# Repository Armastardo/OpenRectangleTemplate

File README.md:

# Open Rectangle Template
**RP2040 template for use with box style controllers for the GC**

## Table of contents
* [About](#about)
* [Usage](#usage)
* [Featured projects](#projects)
* [To-do](#to-do)
* [Acknowledgements](#acknowledgements)

## About
This template was created for the purpose of easing development of box-styled controllers (rectangles) that work with a GameCube console and Nintendo 64 via a USB C to console cable. It uses a RP2040 as its main controller so compatibility to other devices will be limited to the firmware you are using. (Such as [HayBox](https://github.com/JonnyHaystack/HayBox), [Pico-Rectangle](https://github.com/JulienBernard3383279/pico-rectangle), etc). There's already a footprint added for a compatible USB-C port that will allow you to used said cables, as well as a USB C to C cable, or C to A cable for PC or Switch.

Labels are already assigned to the default pinout of the most popular firmware available as well as in stock parts for every component from LCSC. I recommend using the Fabrication Toolkit plugin that can be installed through KiCad's PCM.

## Usage
This templates requires for you to have a minium experience with Kicad and some EE basics. You can just download it as .zip and start creating your own. Make sure you are using **Kicad 7**.
- Download as a zip or clone the repository.
- Open KiCad (7 or newer!) and go to File -> New Project from Template
- Select the tab "User Templates" and click on the Folder icon top right.
- Look for the directory where the kicad project is and open it.
- Template should load. Just click OK and everything will be imported into your project.

## To-do:
- Write a more extensive guide.
- Feature more projects.

## Projects
Small section to highlight proyects that were devveloped using this template.
- [Open Rectangle Breakout](https://github.com/Armastardo/OpenRectangleBreakout) - Breakout board designed to make handwired builds easier.

## Acknowledgements:
- [@Sleepdealr](https://github.com/Sleepdealr/) - For creating the [RP2040 design guide](https://github.com/Sleepdealr/RP2040-designguide) which this template is mostly based from
- Crane's Lab - For having such an amazing community and inspiring creativity in everyone who steps there.
- [@rana-sylvatica](https://github.com/rana-sylvatica/) - For making the OFOF1/Rana Digital and inspiring me to design my rectangles.
- [@Ryanemzed](https://github.com/Ryanemzed/) - For posting a cool clear acrylic build and taking me into a new rabbit hole (and being an amazing community member!).
- The Phob project - For being an amazing standard for the open source-community.

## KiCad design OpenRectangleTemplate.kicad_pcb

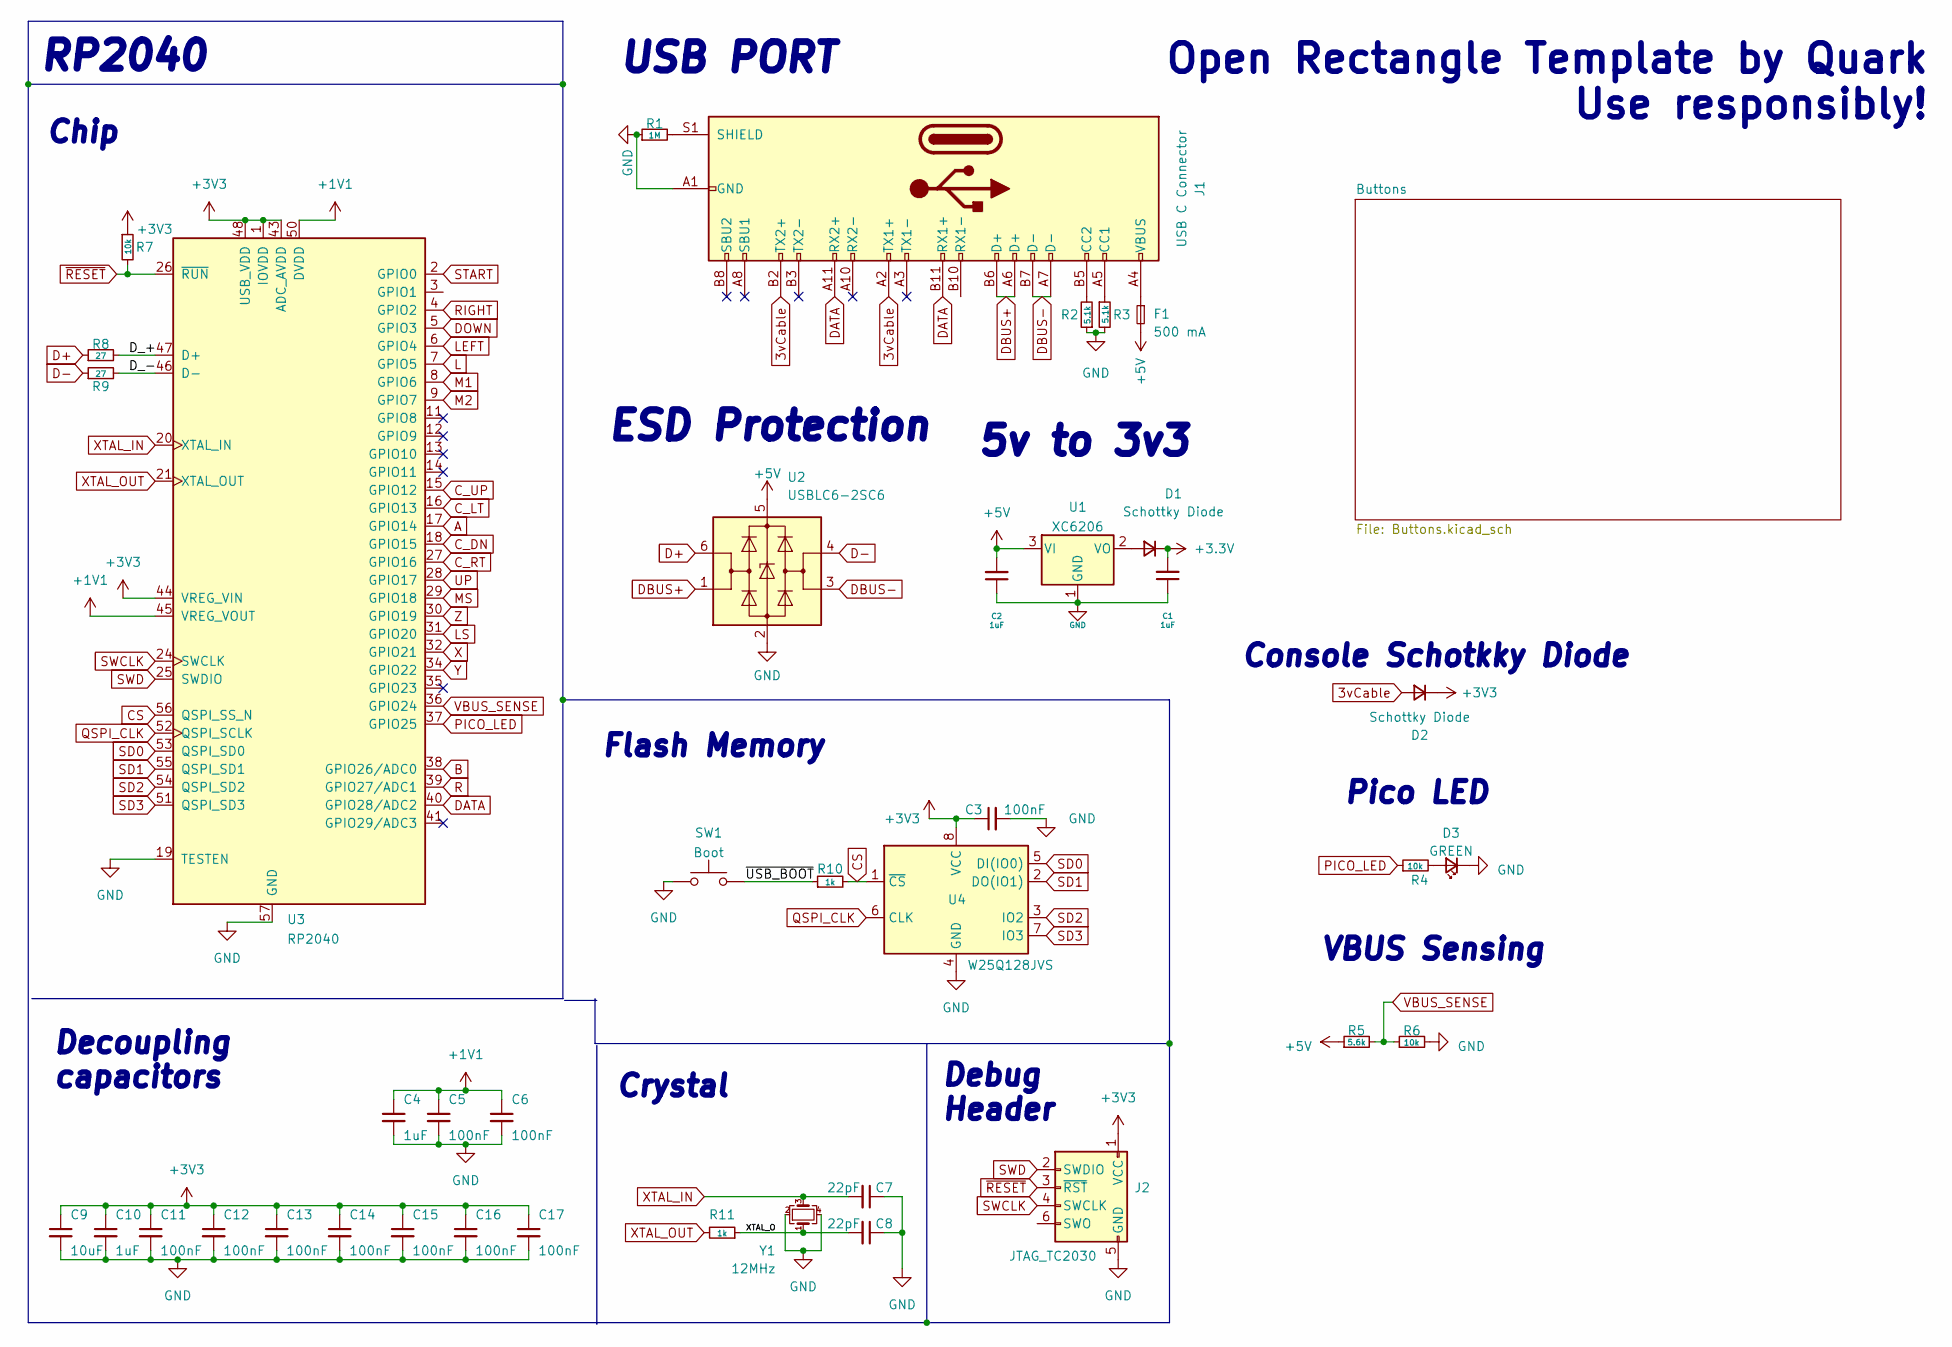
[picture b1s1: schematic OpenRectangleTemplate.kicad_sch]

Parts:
C1, C2, C4, C10: 1uF; C_0402_1005Metric; LCSC C52923
C3, C5, C6, C11, C12, C13, C14, C15, C16, C17: 100nF; C_0402_1005Metric; LCSC C1525
C7, C8: 22pF; C_0402_1005Metric; LCSC C1555
C9: 10uF; C_0402_1005Metric; LCSC C15525
D1, D2: Schottky Diode; D_SOD-123; LCSC C8598
D3: GREEN; LED_0805_2012Metric; LCSC C2297
F1: 500 mA; Fuse_1206_3216Metric; LCSC C70076
J1: USB C Connector; TYPE-C_24P_QCHT; LCSC C456013
J2: JTAG_TC2030; CON_TC2030_outlined
R1: 1M; R_0603_1608Metric; LCSC C22935
R2, R3: 5.1k; R_0402_1005Metric; LCSC C25905
R4, R7: 10k; R_0402_1005Metric; LCSC C25744
R5: 5.6k; R_0603_1608Metric; LCSC C23189
R6: 10k; R_0603_1608Metric; LCSC C25804
R8, R9: 27; R_0603_1608Metric; LCSC C25190
R10, R11: 1k; R_0402_1005Metric; LCSC C11702
SW1: Boot; SW_SPST_SKQG_WithStem; LCSC C318884
U1: XC6206; SOT-23; LCSC C5446
U2: USBLC6-2SC6; SOT-23-6; LCSC C7519
U3: RP2040; RP2040-QFN-56; LCSC C2040
U4: W25Q128JVS; SOIC-8_5.23x5.23mm_P1.27mm; LCSC C97521
Y1: 12MHz; Crystal_SMD_3225-4Pin_3.2x2.5mm; LCSC C9002

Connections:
3vCable: D2.2 (A), J1.A2 (TX1+), J1.B2 (TX2+)
+1V1: C4.1, C5.1, C6.1, U3.23 (DVDD), U3.45 (VREG_VOUT), U3.50 (DVDD)
+5V: C2.2, F1.2, R5.1, U1.3 (VI), U2.5 (VBUS)
/D_+: R8.2, U3.47 (D+)
/D_-: R9.2, U3.46 (D-)
/XTAL_O: C8.2, R11.1, Y1.1
/~USB_BOOT: R10.1, SW1.2
A: U3.17 (GPIO14)
B: U3.38 (GPIO26/ADC0)
CS: R10.2, U3.56 (QSPI_SS_N), U4.1 (~CS)
C_DN: U3.18 (GPIO15)
C_LT: U3.16 (GPIO13)
C_RT: U3.27 (GPIO16)
C_UP: U3.15 (GPIO12)
D+: R8.1, U2.6 (I/O1)
D-: R9.1, U2.4 (I/O2)
DATA: J1.A11 (RX2+), J1.B11 (RX1+), U3.40 (GPIO28/ADC2)
DBUS+: J1.A6 (D+), J1.B6 (D+), U2.1 (I/O1)
DBUS-: J1.A7 (D-), J1.B7 (D-), U2.3 (I/O2)
DOWN: U3.5 (GPIO3)
GND: C1.1, C2.1, C3.2, C4.2, C5.2, C6.2, C7.1, C8.1, C9.2, C10.2, C11.2, C12.2, C13.2, C14.2, C15.2, C16.2, C17.2, D3.1 (K), J1.A1 (GND), J1.A12 (GND), J1.B1 (GND), J1.B12 (GND), J2.5 (GND), R1.1, R2.1, R3.2, R6.2, SW1.1, U1.1 (GND), U2.2 (GND), U3.19 (TESTEN), U3.57 (GND), U4.4 (GND), Y1.2, Y1.4
L: U3.7 (GPIO5)
LEFT: U3.6 (GPIO4)
LS: U3.31 (GPIO20)
M1: U3.8 (GPIO6)
M2: U3.9 (GPIO7)
MS: U3.29 (GPIO18)
unnamed: D1.2 (A), U1.2 (VO)
unnamed: D3.2 (A), R4.2
unnamed: F1.1, J1.A4 (VBUS), J1.A9 (VBUS), J1.B4 (VBUS), J1.B9 (VBUS)
unnamed: J1.A5 (CC1), R3.1
unnamed: J1.B5 (CC2), R2.2
unnamed: J1.S1 (SHIELD), R1.2
PICO_LED: R4.1, U3.37 (GPIO25)
QSPI_CLK: U3.52 (QSPI_SCLK), U4.6 (CLK)
R: U3.39 (GPIO27/ADC1)
RIGHT: U3.4 (GPIO2)
SD0: U3.53 (QSPI_SD0), U4.5 (DI(IO0))
SD1: U3.55 (QSPI_SD1), U4.2 (DO(IO1))
SD2: U3.54 (QSPI_SD2), U4.3 (IO2)
SD3: U3.51 (QSPI_SD3), U4.7 (IO3)
START: U3.2 (GPIO0)
SWCLK: J2.4 (SWCLK), U3.24 (SWCLK)
SWD: J2.2 (SWDIO), U3.25 (SWDIO)
UP: U3.28 (GPIO17)
VBUS_SENSE: R5.2, R6.1, U3.36 (GPIO24)
X: U3.32 (GPIO21)
XTAL_IN: C7.2, U3.20 (XTAL_IN), Y1.3
XTAL_OUT: R11.2, U3.21 (XTAL_OUT)
Y: U3.34 (GPIO22)
Z: U3.30 (GPIO19)
~RESET: J2.3 (~RST), R7.2, U3.26 (~RUN)

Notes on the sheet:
Console Schotkky Diode
Crystal
USB PORT
Flash Memory
Pico LED
Open Rectangle Template by Quark Use responsibly!
RP2040
Debug Header
VBUS Sensing
Chip
5v to 3v3
ESD Protection
Decoupling capacitors

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
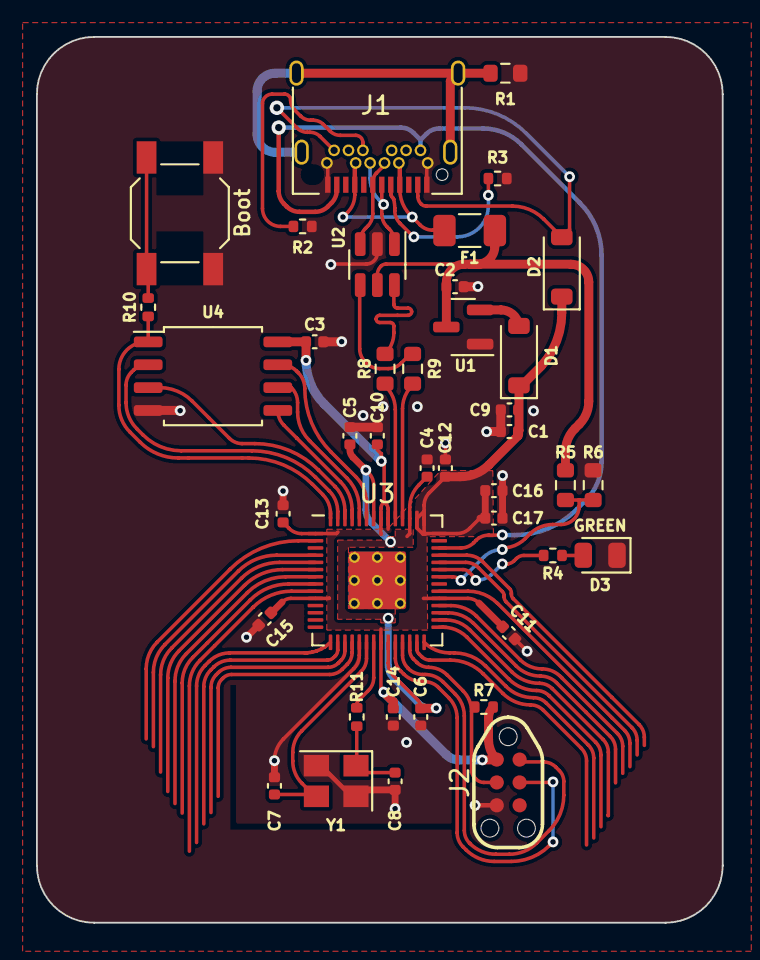
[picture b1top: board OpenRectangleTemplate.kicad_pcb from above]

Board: 2 copper layers, 38.1 x 49.2 mm, 40 parts (0 on the bottom side), 33 nets.

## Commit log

2023-02-21 Updated pictures, added schematic
2023-02-21 Reverted back to pico pinout
2023-02-21 Updated render and small changes
2023-03-23 Prototyped and tested
2023-07-24 Adjusted the schematic to the correct grid
2023-08-13 Adjusted part numbers
2023-08-13 Updated 3D models and footprints
2024-02-28 Actually a template now
